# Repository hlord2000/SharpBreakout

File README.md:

# Sharp Memory-in-Pixel Display Breakout for the nRF54L15-DK

Supports the following displays (with Molex 503566-2102 or 503566-2100 FPC connector):

- 30mm round, 240x240px [LS012B7DD06A](https://www.sharpsde.com/products/displays/model/ls012b7dd06a/#productview)
- 32mm round, 260x260px [LS013B7DD02](https://www.sharpsde.com/products/displays/model/ls012b7dd06a-1/#productview)
- 35mm round, 280x280px [LS014B7DD01](https://www.sharpsde.com/products/displays/model/ls012b7dd06a-1-1/)
- 55mm rectangular, 320x240px [LS021B7DD02](https://www.sharpsde.com/products/displays/model/ls012b7dd06a-1-1-1/#productview)

# Schematic

# Bill of Material

|Reference  |Qty|Value              |Footprint                                                 |
|-----------|---|-------------------|----------------------------------------------------------|
|C1,C2,C3,C5|4  |1uF                |Capacitor_SMD:C_0805_2012Metric                           |
|C4,C6      |2  |100nF              |Capacitor_SMD:C_0805_2012Metric                           |
|J1         |1  |Molex 503566-2102  |SharpBreakout-Connector_FFC-FPC:5035662102                |
|J2,J6      |2  |Conn_01x02_Pin     |Connector_PinHeader_2.54mm:PinHeader_1x02_P2.54mm_Vertical|
|J3,J5      |2  |Conn_02x10_Odd_Even|Connector_PinHeader_2.54mm:PinHeader_2x10_P2.54mm_Vertical|
|J4         |1  |Conn_02x02_Odd_Even|Connector_PinHeader_2.54mm:PinHeader_2x02_P2.54mm_Vertical|
|U1,U2      |2  |SiP32431DR3        |Package_TO_SOT_SMD:SOT-363_SC-70-6                        |

# Pinout

| nRF54L15-DK Pin | Sharp Display Pin |
|-----------------|------------------|
| P0.00 | R1 |
| P0.01 | BCK |
| P0.02 | B1 |
| P0.03 | G1 |
| P0.04 | VCOM/VB |
| P1.04 | VBUS_EN (VDD2_EN) |
| P1.05 | VDDIO_EN (VDD1_EN) |
| P1.06 | GCK |
| P1.07 | INTB |
| P1.08 | VA |
| P1.09 | GSP |
| P1.10 | GEN |
| P1.11 | BSP |
| P1.12 | R0 |
| P1.13 | G0 |
| P1.14 | B0 |

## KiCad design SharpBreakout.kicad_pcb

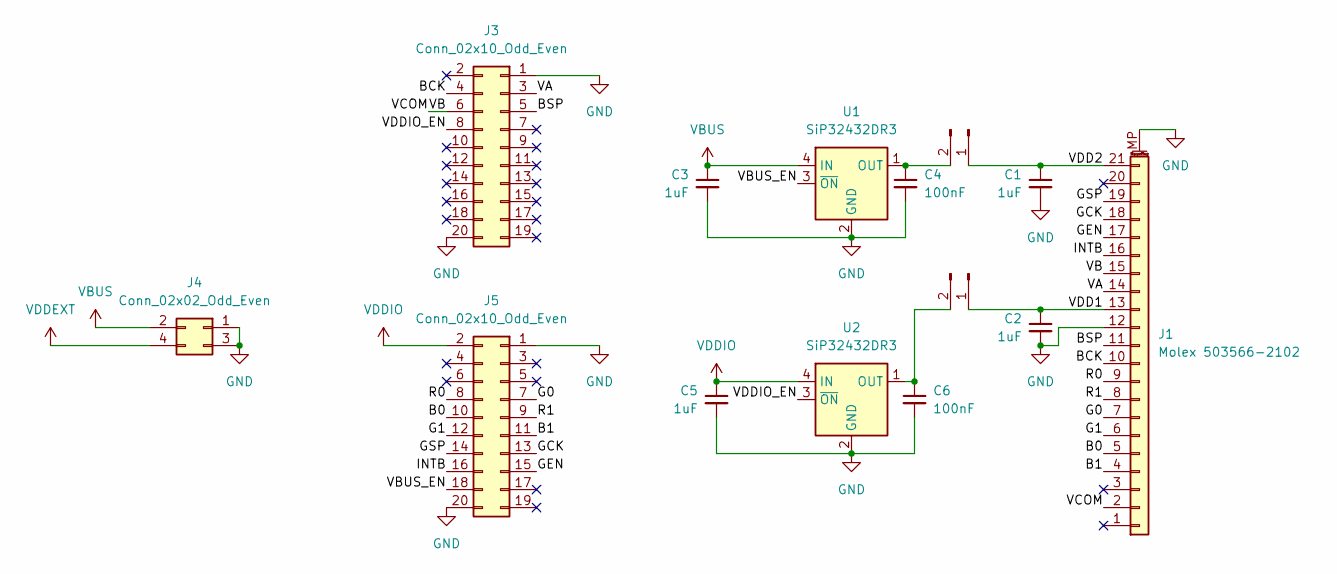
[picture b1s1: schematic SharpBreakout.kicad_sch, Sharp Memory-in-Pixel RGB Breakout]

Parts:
C1, C2, C3, C5: 1uF; C_0805_2012Metric
C4, C6: 100nF; C_0805_2012Metric
J1: Molex 503566-2102; 5035662102
J2, J6: Conn_01x02_Pin; PinHeader_1x02_P2.54mm_Vertical
J3, J5: Conn_02x10_Odd_Even; PinHeader_2x10_P2.54mm_Vertical
J4: Conn_02x02_Odd_Even; PinHeader_2x02_P2.54mm_Vertical
U1, U2: SiP32432DR3; SOT-363_SC-70-6

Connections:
/B0: J1.5, J5.10
/B1: J1.4, J5.11
/BCK: J1.10, J3.4
/BSP: J1.11, J3.5
/G0: J1.7, J5.7
/G1: J1.6, J5.12
/GCK: J1.18, J5.13
/GEN: J1.17, J5.15
/GSP: J1.19, J5.14
/INTB: J1.16, J5.16
/R0: J1.9, J5.8
/R1: J1.8, J5.9
/VA: J1.14, J3.3
/VB: J1.2, J1.15, J3.6
/VBUS_EN: J5.18, U1.3 (~ON)
/VDD1: C2.1, J1.13, J6.1
/VDD2: C1.1, J1.21, J2.1
/VDDIO_EN: J3.8, U2.3 (~ON)
GND: C1.2, C2.2, C3.2, C4.2, C5.2, C6.2, J1.12, J1.MP (MountPin), J3.1, J3.20, J4.1, J4.3, J5.1, J5.20, U1.2 (GND), U1.5 (GND), U2.2 (GND), U2.5 (GND)
unnamed: C4.1, J2.2, U1.1 (OUT)
unnamed: C6.1, J6.2, U2.1 (OUT)
VBUS: C3.1, J4.2, U1.4 (IN)
VDDEXT: J4.4
VDDIO: C5.1, J5.2, U2.4 (IN)

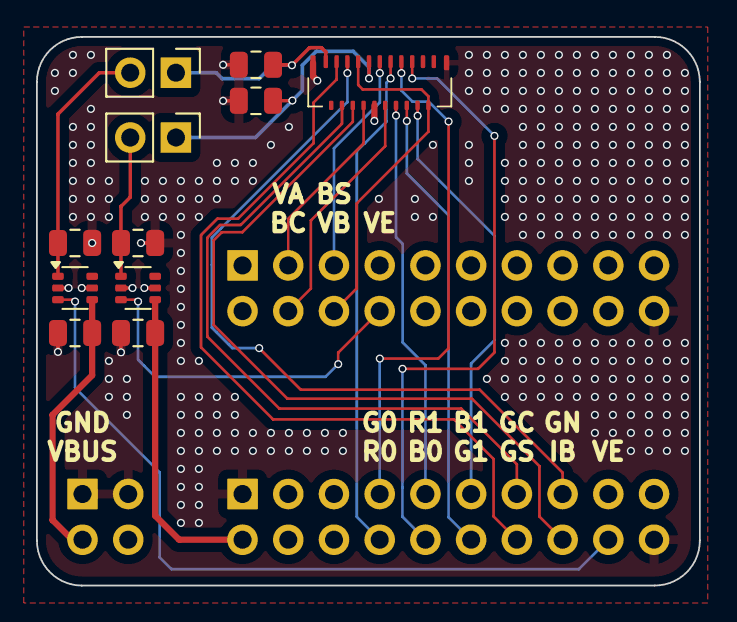
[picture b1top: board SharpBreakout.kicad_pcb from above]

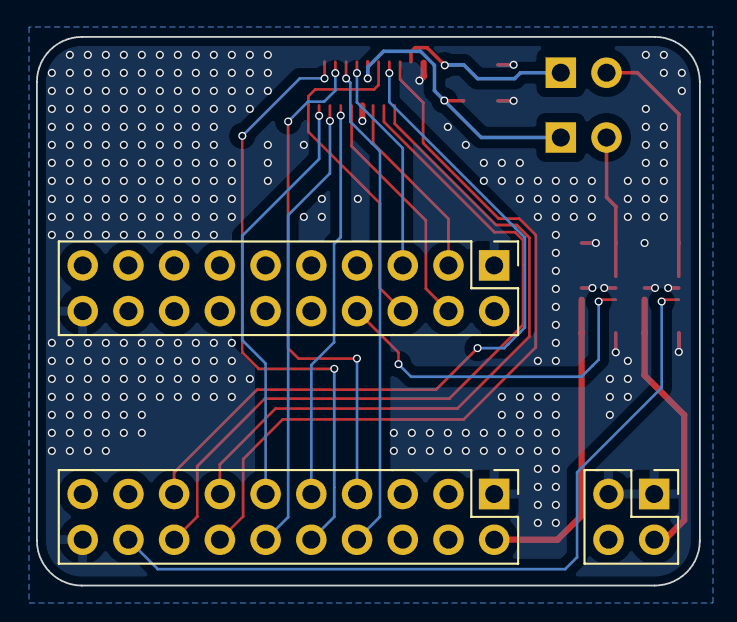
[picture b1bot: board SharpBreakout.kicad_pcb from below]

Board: 4 copper layers, 36.8 x 30.5 mm, 14 parts (3 on the bottom side), 23 nets.

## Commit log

2025-02-17 Initial commit.
2025-02-17 Added README and pinout
2025-04-06 Updated pinout for better performance, all colors on one GPIO periphral, all horizontal controls on same GPIO peripheral, all vertical controls on same GPIO peripheral
